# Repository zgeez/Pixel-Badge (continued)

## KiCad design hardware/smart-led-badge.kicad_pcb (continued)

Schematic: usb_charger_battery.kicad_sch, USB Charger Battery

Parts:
C301, C302: 100nF; C_0402_1005Metric; MPN CL05B104KO5NNNC; LCSC C1525
C303: 1uF 50V; C_0603_1608Metric; MPN CL10A105KB8NNNC; LCSC C15849
C304, C309: 10uF 25V; C_0805_2012Metric; MPN CL21A106KAYNNNE; LCSC C15850
C305: 47nF 16V; C_0402_1005Metric; MPN CL05B473KO5NNNC; LCSC C307434
C306: 4.7uF 16V; C_0603_1608Metric; MPN CL10A475KO8NNNC; LCSC C19666
C307, C308: 22uF 25V; C_0805_2012Metric; MPN CL21A226MAQNNNE; LCSC C45783
J301: TYPE-C-31-M-12; USB_C_Receptacle_HRO_TYPE-C-31-M-12; MPN TYPE-C-31-M-12; LCSC C165948
J302: Battery JST-PH 2P; JST_PH_S2B-PH-K_1x02_P2.00mm_Horizontal; MPN S2B-PH-K-S(LF)(SN); LCSC C173752
L301: 1uH; L_Coilcraft_XGL4020; MPN XGL4020-102MEC; LCSC C5357696
Q301, Q302, Q303: AO3400A; SOT-23; MPN AO3400A; LCSC C20917
R301, R302: 5.1k; R_0402_1005Metric; MPN 0402WGF5101TCE; LCSC C25905
R303, R306, R313, R316: 100k; R_0402_1005Metric; MPN 0402WGF1003TCE; LCSC C25741
R304, R307: 12k; R_0402_1005Metric; MPN 0402WGF1202TCE; LCSC C25752
R309, R311, R312: 10k; R_0402_1005Metric; MPN 0402WGF1002TCE; LCSC C25744
R314, R315: 4.7k; R_0402_1005Metric; MPN 0402WGF4701TCE; LCSC C25900
TH301: 10k B3380/3434; R_0402_1005Metric; MPN NCP15XH103F03RC; LCSC C77131
TP301: VBUS; TestPoint_Pad_D0.8mm
TP305: TS; TestPoint_Pad_D1.0mm
TP307: QON; TestPoint_Pad_D1.0mm
TP308: CHG_STAT; TestPoint_Pad_D1.0mm
TP309: CC1; TestPoint_Pad_D1.0mm
TP310: CC2; TestPoint_Pad_D1.0mm
TP311: GND; TestPoint_Pad_D0.8mm
U301: TPD4E05U06; TI_DQA0010A_USON-10_2.5x1.0mm_P0.5mm; MPN TPD4E05U06DQAR; LCSC C138714
U302: BQ25620; Texas_RYK0018A; MPN BQ25620RYKR; LCSC C6164243

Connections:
+3V3: Q301.1 (G), Q302.1 (G), R311.2, R312.2, R314.2, R315.2; also elsewhere on the board
/USB Charger Battery/BTST: C305.1, U302.1 (BTST)
/USB Charger Battery/CC1: J301.A5 (CC1), R301.1, R303.1, TP309.1, U301.4 (D2+)
/USB Charger Battery/CC1_HV: Q301.3 (D), R303.2
/USB Charger Battery/CC2: J301.B5 (CC2), R302.1, R306.1, TP310.1, U301.5 (D2-)
/USB Charger Battery/CC2_HV: Q302.3 (D), R306.2
/USB Charger Battery/PMID: C304.1, U302.17 (PMID)
/USB Charger Battery/QON: TP307.1, U302.7 (QON)
/USB Charger Battery/REGN: C306.1, R309.1, U302.2 (REGN)
/USB Charger Battery/SW_CHG: C305.2, L301.1, U302.16 (SW)
/USB Charger Battery/TS: R309.2, TH301.1, TP305.1, U302.6 (TS)
CC1_SENSE: C301.1, Q301.2 (S), R304.1; also elsewhere on the board
CC2_SENSE: C302.1, Q302.2 (S), R307.1; also elsewhere on the board
CHG_CE: Q303.3 (D), R313.1, U302.14 (CE)
CHG_EN: Q303.1 (G), R316.1; also elsewhere on the board
CHG_INT: R312.1, U302.11 (INT); also elsewhere on the board
CHG_PG_N: U302.3 (PG); also elsewhere on the board
CHG_STAT: R311.1, TP308.1, U302.10 (STAT)
GND: C301.2, C302.2, C303.2, C304.2, C306.2, C307.2, C308.2, C309.2, J301.A1 (GND), J301.A12 (GND), J301.B1 (GND), J301.B12 (GND), J301.SH (SHIELD), J302.1, Q303.2 (S), R301.2, R302.2, R304.2, R307.2, R316.2, TH301.2, TP311.1, U301.3 (GND), U301.8 (GND), U302.15 (GND); also elsewhere on the board
I2C1_SCL: R315.1, U302.13 (SCL); also elsewhere on the board
I2C1_SDA: R314.1, U302.12 (SDA); also elsewhere on the board
SYS: C307.1, C308.1, L301.2, R313.2, U302.9 (SYS); also elsewhere on the board
USB_DN: J301.A7 (D-), J301.B7 (D-), U301.2 (D1-), U302.4 (D-); also elsewhere on the board
USB_DP: J301.A6 (D+), J301.B6 (D+), U301.1 (D1+), U302.5 (D+); also elsewhere on the board
VBAT: C309.1, J302.2, U302.8 (BAT); also elsewhere on the board
VBUS: C303.1, J301.A4 (VBUS), J301.A9 (VBUS), J301.B4 (VBUS), J301.B9 (VBUS), TP301.1, U302.18 (VBUS); also elsewhere on the board

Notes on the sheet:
USB-C, charger and battery (Rev A) - design notes USB-C sink, USB 2.0, no PD: independent 5.1k Rd on CC1/CC2; TPD4E05U06 on D+, D-, CC1, CC2. CC sense: firmware reads CC1/CC2 via SAADC (ratio 0.107) and raises the BQ25620 input limit only on a valid >= 1.5 A advertisement; SDP/unknown sources stay 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

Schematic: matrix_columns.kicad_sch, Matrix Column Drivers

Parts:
C601, C603: 100nF; C_0402_1005Metric; MPN CL05B104KO5NNNC; LCSC C1525
C602, C604: 1uF; C_0402_1005Metric; MPN CL05A105KA5NQNC; LCSC C52923
R601, R603: 2.94k; R_0402_1005Metric; MPN 0402WGF2941TCE; LCSC C25886
R602, R604: 0; R_0402_1005Metric; MPN 0402WGF0000TCE; LCSC C17168
TP601: COL0; TestPoint_Pad_D1.0mm
TP605: MTX_SCK; TestPoint_Pad_D1.0mm
TP607: MTX_LAT; TestPoint_Pad_D1.0mm
U601, U602: TLC59283; Texas_RGE0024C_VQFN-24-1EP_4x4mm_P0.5mm_EP2.1x2.1mm_Thermal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; MPN TLC59283RGER; LCSC C485815

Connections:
+3V3: C601.1, C602.1, C603.1, C604.1, U601.21 (VCC), U602.21 (VCC); also elsewhere on the board
/Matrix Column Drivers/IREF1: R601.1, U601.20 (IREF)
/Matrix Column Drivers/IREF1_LO: R601.2, R602.1
/Matrix Column Drivers/IREF2: R603.1, U602.20 (IREF)
/Matrix Column Drivers/IREF2_LO: R603.2, R604.1
/Matrix Column Drivers/TLC_CHAIN: U601.19 (SOUT), U602.23 (SIN)
BLANK_TLC: U601.18 (BLANK), U602.18 (BLANK); also elsewhere on the board
COL0: TP601.1, U601.2 (OUT0); also elsewhere on the board
COL1: U601.3 (OUT1); also elsewhere on the board
COL2: U601.4 (OUT2); also elsewhere on the board
COL3: U601.5 (OUT3); also elsewhere on the board
COL4: U601.6 (OUT4); also elsewhere on the board
COL5: U601.7 (OUT5); also elsewhere on the board
COL6: U601.8 (OUT6); also elsewhere on the board
COL7: U601.9 (OUT7); also elsewhere on the board
COL8: U601.10 (OUT8); also elsewhere on the board
COL9: U601.11 (OUT9); also elsewhere on the board
COL10: U601.12 (OUT10); also elsewhere on the board
COL11: U601.13 (OUT11); also elsewhere on the board
COL12: U601.14 (OUT12); also elsewhere on the board
COL13: U601.15 (OUT13); also elsewhere on the board
COL14: U601.16 (OUT14); also elsewhere on the board
COL15: U601.17 (OUT15); also elsewhere on the board
COL16: U602.2 (OUT0); also elsewhere on the board
COL17: U602.3 (OUT1); also elsewhere on the board
COL18: U602.4 (OUT2); also elsewhere on the board
COL19: U602.5 (OUT3); also elsewhere on the board
COL20: U602.6 (OUT4); also elsewhere on the board
COL21: U602.7 (OUT5); also elsewhere on the board
COL22: U602.8 (OUT6); also elsewhere on the board
COL23: U602.9 (OUT7); also elsewhere on the board
COL24: U602.10 (OUT8); also elsewhere on the board
COL25: U602.11 (OUT9); also elsewhere on the board
COL26: U602.12 (OUT10); also elsewhere on the board
COL27: U602.13 (OUT11); also elsewhere on the board
COL28: U602.14 (OUT12); also elsewhere on the board
COL29: U602.15 (OUT13); also elsewhere on the board
COL30: U602.16 (OUT14); also elsewhere on the board
COL31: U602.17 (OUT15); also elsewhere on the board
GND: C601.2, C602.2, C603.2, C604.2, R602.2, R604.2, U601.22 (GND), U601.25 (EP), U602.22 (GND), U602.25 (EP); also elsewhere on the board
MTX_LAT: TP607.1, U601.1 (LAT), U602.1 (LAT); also elsewhere on the board
MTX_MISO: U602.19 (SOUT); also elsewhere on the board
MTX_MOSI: U601.23 (SIN); also elsewhere on the board
MTX_SCK: TP605.1, U601.24 (SCLK), U602.24 (SCLK); also elsewhere on the board

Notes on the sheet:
Matrix column drivers (Rev A) - design notes 2 x TI TLC59283 (SBVS199C), RGE VQFN-24, VCC = 3V3, cascaded: MOSI -> U601 SIN, U601 SOUT -> U602 SIN, U602 SOUT -> MTX_MISO (SPIM3 readback) and the row-chain SER (row sheet). SCLK = MTX_SCK, LAT = MTX_LAT (also latches the row 595s). BLANK = BLANK_TLC 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

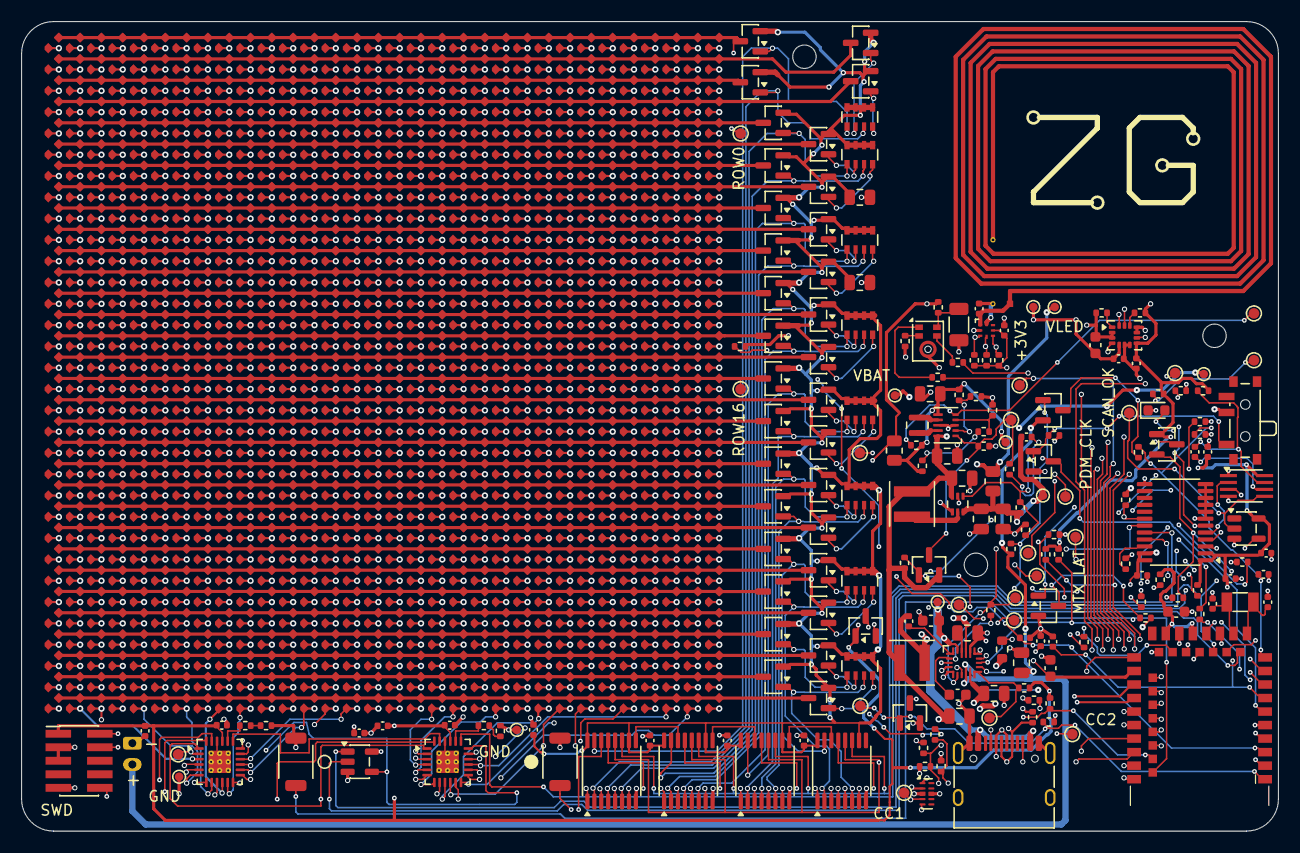
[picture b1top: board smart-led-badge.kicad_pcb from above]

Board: 4 copper layers, 118.0 x 76.0 mm, 1236 parts (1 on the bottom side), 194 nets.

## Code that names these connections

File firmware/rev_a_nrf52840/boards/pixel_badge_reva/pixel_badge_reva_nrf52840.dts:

/* SPDX-License-Identifier: MIT */
/dts-v1/;
#include <nordic/nrf52840_qiaa.dtsi>
#include <zephyr/dt-bindings/gpio/nordic-nrf-gpio.h>
#include <zephyr/dt-bindings/input/input-event-codes.h>
#include <zephyr/dt-bindings/adc/adc.h>
#include <zephyr/dt-bindings/sensor/icm42688.h>
#include "pixel_badge_reva_nrf52840-pinctrl.dtsi"

/ {
	model = "Pixel Badge Rev A E73 nRF52840";
	compatible = "smart-led-badge,rev-a-nrf52840";
	chosen {
		zephyr,sram = &sram0;
		zephyr,flash = &flash0;
		zephyr,code-partition = &slot0_partition;
		zephyr,display = &matrix0;
	};
	leds {
		compatible = "gpio-leds";
		status_led: status_led { gpios = <&gpio0 28 GPIO_ACTIVE_HIGH>; };
	};
	buttons {
		compatible = "gpio-keys";
		btn_mode: mode { gpios = <&gpio1 6 (GPIO_ACTIVE_LOW | GPIO_PULL_UP)>; zephyr,code = <INPUT_KEY_0>; };
		btn_action: action { gpios = <&gpio1 10 (GPIO_ACTIVE_LOW | GPIO_PULL_UP)>; zephyr,code = <INPUT_KEY_1>; };
	};
	matrix0: matrix {
		compatible = "smartledbadge,reva-matrix";
		width = <32>;
		height = <32>;
		spi = <&spi3>;
		timer = <&timer3>;
		/* Scan SPIM2 drives the same SCK/MOSI pins as spi3_default. */
		scan-spim = <&spi2>;
		plane-timer = <&timer4>;
		sck-gpios = <&gpio0 12 GPIO_ACTIVE_HIGH>;
		mosi-gpios = <&gpio0 4 GPIO_ACTIVE_HIGH>;
		lat-gpios = <&gpio1 9 GPIO_ACTIVE_HIGH>;
		blank-gpios = <&gpio0 5 GPIO_ACTIVE_HIGH>;
		arm-gpios = <&gpio0 6 GPIO_ACTIVE_HIGH>;
		safe-gpios = <&gpio0 26 GPIO_ACTIVE_HIGH>;
		enable-gpios = <&gpio0 7 GPIO_ACTIVE_HIGH>;
	};
	zephyr,user {
		mtx-lat-gpios = <&gpio1 9 GPIO_ACTIVE_HIGH>;
		mtx-blank-gpios = <&gpio0 5 GPIO_ACTIVE_HIGH>;
		mtx-arm-gpios = <&gpio0 6 GPIO_ACTIVE_HIGH>;
		mtx-safe-gpios = <&gpio0 26 GPIO_ACTIVE_HIGH>;
		led-en-gpios = <&gpio0 7 GPIO_ACTIVE_HIGH>;
		vbat-meas-en-gpios = <&gpio1 11 GPIO_ACTIVE_HIGH>;
		chg-en-gpios = <&gpio0 31 GPIO_ACTIVE_HIGH>;
		chg-int-gpios = <&gpio1 4 GPIO_ACTIVE_LOW>;
		pwr-sw-gpios = <&gpio1 13 (GPIO_ACTIVE_LOW | GPIO_PULL_UP)>;
		ntag-i2c-bus = <&i2c1>;
		charger-i2c-bus = <&i2c0>;
		nfc-pwr-gpios = <&gpio1 0 (GPIO_ACTIVE_HIGH | NRF_GPIO_DRIVE_H0H1)>;
		nfc-fd-gpios = <&gpio1 2 GPIO_ACTIVE_LOW>;
		imu-int2-gpios = <&gpio0 10 GPIO_ACTIVE_HIGH>;
		io-channels = <&adc 0>, <&adc 1>, <&adc 2>, <&adc 3>;
		io-channel-names = "vbat", "cc1", "cc2", "vled";
	};
	aliases { led0 = &status_led; sw0 = &btn_mode; sw1 = &btn_action; watchdog0 = &wdt0; imu0 = &imu; };
};
/* VDDH=VDD, normal-voltage supply; external LF load capacitors on the PCB. */
&reg0 { status = "disabled"; };
/* REG1 retains its default LDO mode during initial bring-up. */
&uicr { gpio-as-nreset; nfct-pins-as-gpios; };
&gpiote { status = "okay"; };
&gpio0 { status = "okay"; };
&gpio1 { status = "okay"; };
&timer3 { status = "okay"; };
&spi3 {
	compatible = "nordic,nrf-spim";
	status = "okay";
	pinctrl-0 = <&spi3_default>; pinctrl-1 = <&spi3_sleep>; pinctrl-names = "default", "sleep";
};
&i2c0 {
	compatible = "nordic,nrf-twim";
	/* Standard mode: at 400 kHz the BQ25620 in low-power mode needs >= 68 us
	 * bus-free and repeated-START setup time (SLUSEG2D 8.5), which TWIM
	 * cannot insert; 100 kHz has no extra requirement. */
	status = "okay"; clock-frequency = <I2C_BITRATE_STANDARD>;
	pinctrl-0 = <&i2c0_default>; pinctrl-1 = <&i2c0_sleep>; pinctrl-names = "default", "sleep";
	imu: icm42688@68 {
		compatible = "invensense,icm42688p-i2c"; reg = <0x68>;
		int-gpios = <&gpio0 9 GPIO_ACTIVE_HIGH>;
		accel-pwr-mode = <ICM42688_DT_ACCEL_LN>; accel-odr = <ICM42688_DT_ACCEL_ODR_100>; accel-fs = <ICM42688_DT_ACCEL_FS_2>;
		gyro-pwr-mode = <ICM42688_DT_GYRO_LN>; gyro-odr = <ICM42688_DT_GYRO_ODR_100>; gyro-fs = <ICM42688_DT_GYRO_FS_2000>;
	};
	/* BQ25620 at 0x6B shares this bus (zephyr,user charger-i2c-bus). */
};
&i2c1 {
	compatible = "nordic,nrf-twim";
	status = "okay"; clock-frequency = <I2C_BITRATE_STANDARD>;
	pinctrl-0 = <&i2c1_default>; pinctrl-1 = <&i2c1_sleep>; pinctrl-names = "default", "sleep";
};
/* E73 USB: D+ pin 31, D- pin 29, VBUS pin 27 (docs/power.md). The firmware's
 * only USB function is an inert CDC ACM interface that lets the host configure
 * the badge for the 500 mA SDP input limit. */
zephyr_udc0: &usbd {
	compatible = "nordic,nrf-usbd";
	status = "okay";
	cdc_acm_uart0: cdc_acm_uart0 {
		compatible = "zephyr,cdc-acm-uart";
	};
};
&pdm0 { status = "okay"; pinctrl-0 = <&pdm0_default>; pinctrl-1 = <&pdm0_sleep>; pinctrl-names = "default", "sleep"; };
&adc {
	status = "okay"; #address-cells = <1>; #size-cells = <0>;
	channel@0 { reg = <0>; zephyr,gain = "ADC_GAIN_1_4"; zephyr,reference = "ADC_REF_INTERNAL"; zephyr,acquisition-time = <ADC_ACQ_TIME(ADC_ACQ_TIME_MICROSECONDS, 10)>; zephyr,input-positive = <NRF_SAADC_AIN6>; zephyr,resolution = <12>; };
	channel@1 { reg = <1>; zephyr,gain = "ADC_GAIN_2"; zephyr,reference = "ADC_REF_INTERNAL"; zephyr,acquisition-time = <ADC_ACQ_TIME(ADC_ACQ_TIME_MICROSECONDS, 10)>; zephyr,input-positive = <NRF_SAADC_AIN0>; zephyr,resolution = <12>; };
	channel@2 { reg = <2>; zephyr,gain = "ADC_GAIN_2"; zephyr,reference = "ADC_REF_INTERNAL"; zephyr,acquisition-time = <ADC_ACQ_TIME(ADC_ACQ_TIME_MICROSECONDS, 10)>; zephyr,input-positive = <NRF_SAADC_AIN1>; zephyr,resolution = <12>; };
	channel@3 { reg = <3>; zephyr,gain = "ADC_GAIN_4"; zephyr,reference = "ADC_REF_INTERNAL"; zephyr,acquisition-time = <ADC_ACQ_TIME(ADC_ACQ_TIME_MICROSECONDS, 10)>; zephyr,input-positive = <NRF_SAADC_AIN5>; zephyr,resolution = <12>; };
};
&flash0 {
	partitions {
		compatible = "fixed-partitions"; #address-cells = <1>; #size-cells = <1>;
		boot_partition: partition@0 { label = "mcuboot"; reg = <0x0 0x10000>; };
		slot0_partition: partition@10000 { label = "image-0"; reg = <0x10000 0x50000>; };
		slot1_partition: partition@60000 { label = "image-1"; reg = <0x60000 0x50000>; };
		artwork_storage: partition@b0000 { label = "artwork-storage"; reg = <0xb0000 0x42000>; };
		reserved_partition: partition@f2000 { label = "reserved"; reg = <0xf2000 0x6000>; };
		storage_partition: partition@f8000 { label = "storage"; reg = <0xf8000 0x8000>; };
	};
};
